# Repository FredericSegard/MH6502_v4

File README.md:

# MH6502-4
 This is my masterpiece MH6502-4.

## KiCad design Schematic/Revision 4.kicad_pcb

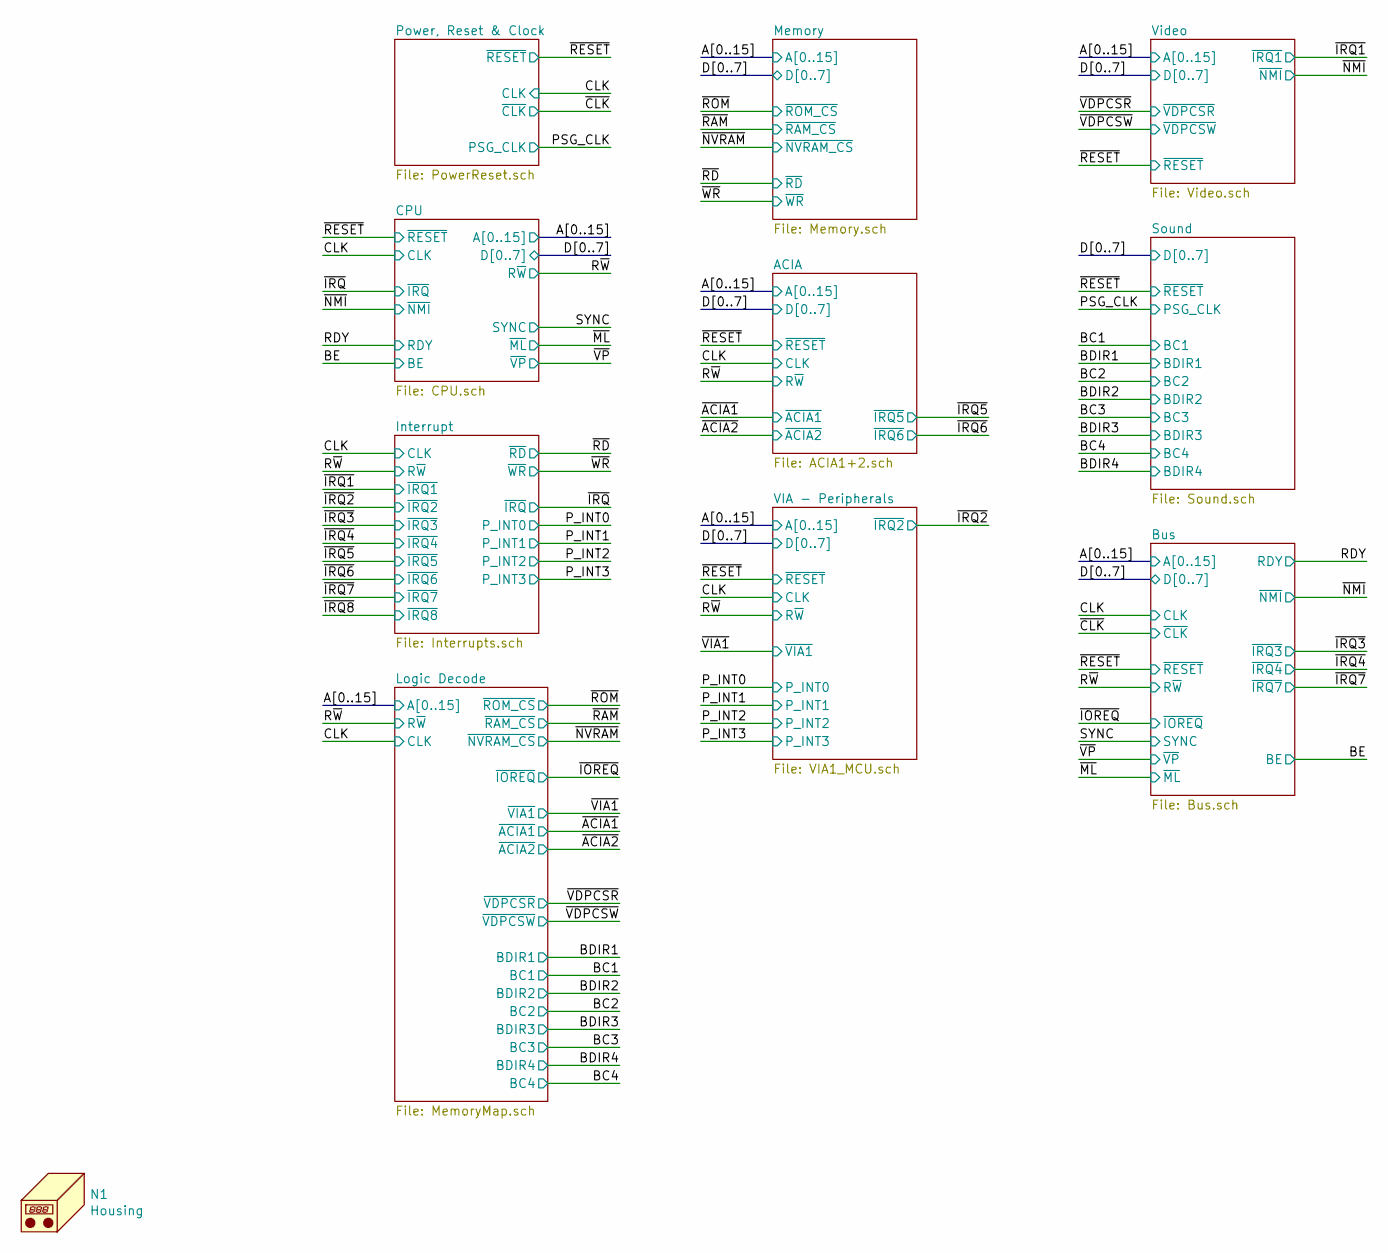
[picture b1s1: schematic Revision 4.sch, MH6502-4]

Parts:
N1: Housing; 18877_Housing

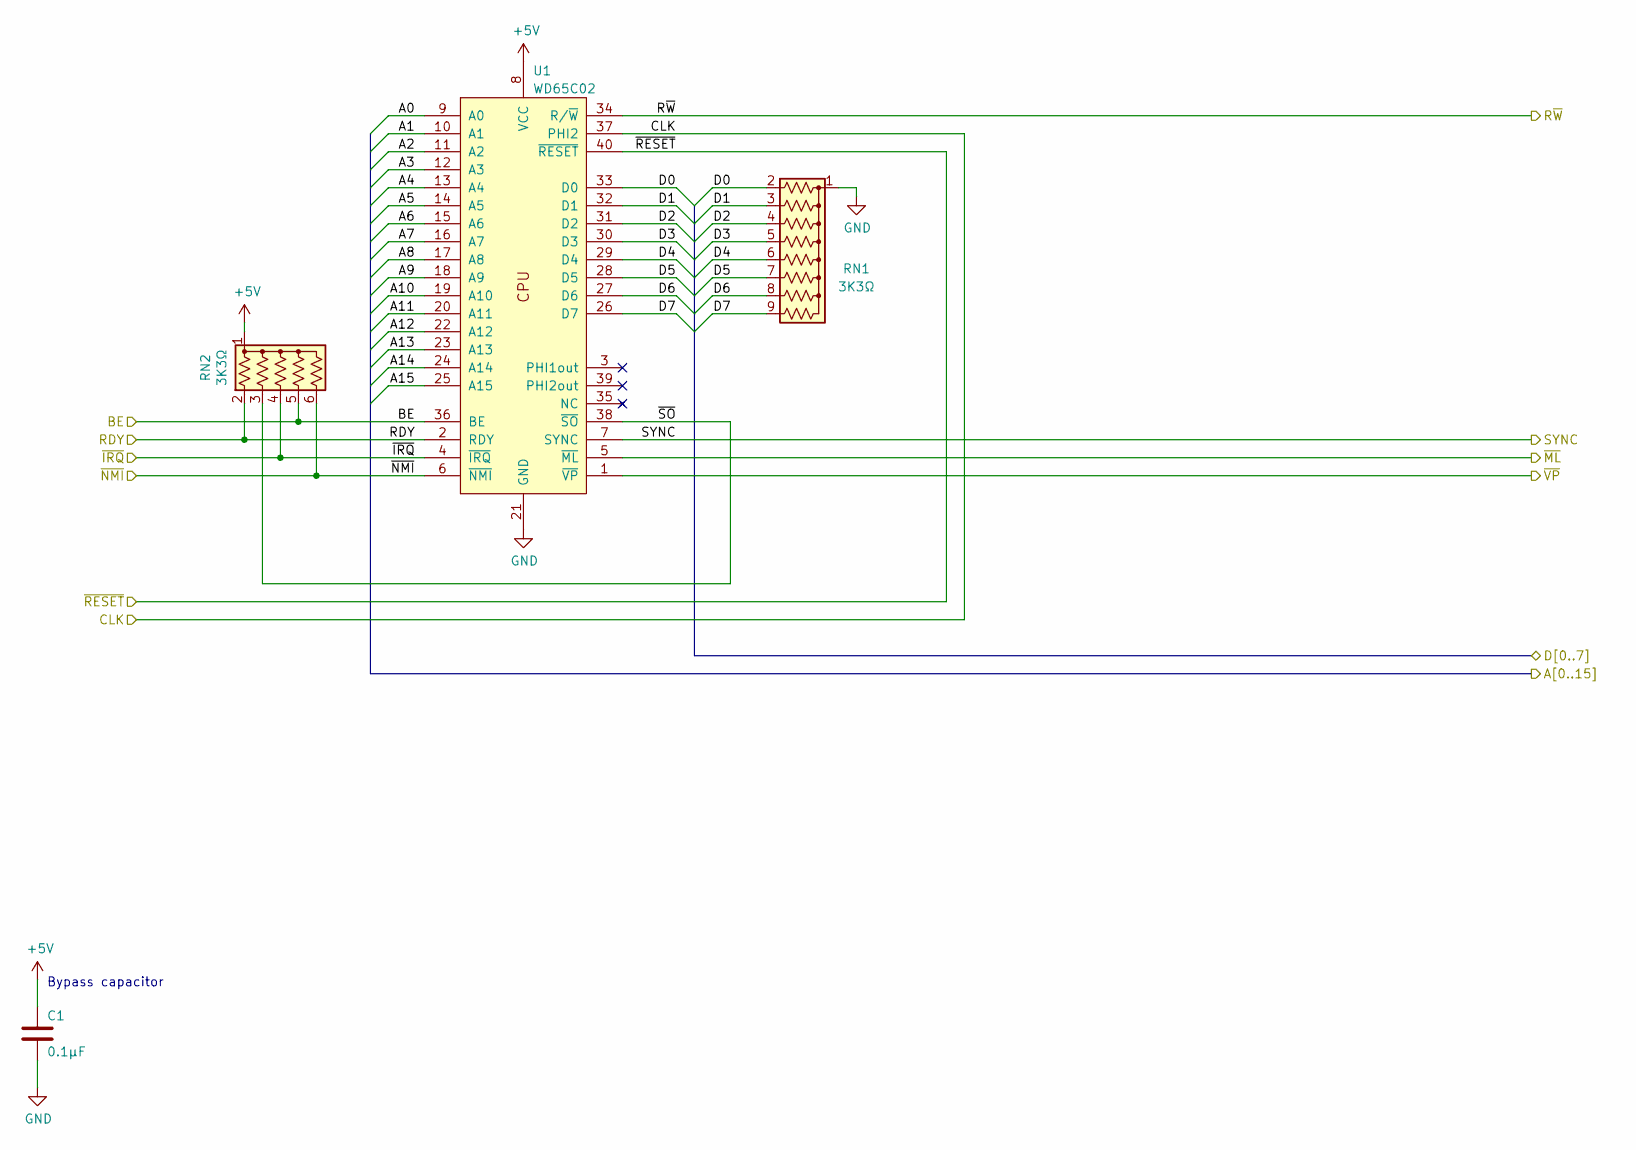
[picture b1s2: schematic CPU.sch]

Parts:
C1: 0.1µF; C_Disc_D3.0mm_W1.6mm_P2.50mm
RN1: 3K3Ω; R_Array_SIP9
RN2: 3K3Ω; R_Array_SIP6
U1: WD65C02; DIP-40_W15.24mm_Socket

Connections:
+5V: C1.1, RN2.1 (common), U1.8 (VCC); also elsewhere on the board
/ACIA/A0: U1.9 (A0); also elsewhere on the board
/ACIA/A1: U1.10 (A1); also elsewhere on the board
/ACIA/D0: RN1.2 (R1), U1.33 (D0); also elsewhere on the board
/ACIA/D1: RN1.3 (R2), U1.32 (D1); also elsewhere on the board
/ACIA/D2: RN1.4 (R3), U1.31 (D2); also elsewhere on the board
/ACIA/D3: RN1.5 (R4), U1.30 (D3); also elsewhere on the board
/ACIA/D4: RN1.6 (R5), U1.29 (D4); also elsewhere on the board
/ACIA/D5: RN1.7 (R6), U1.28 (D5); also elsewhere on the board
/ACIA/D6: RN1.8 (R7), U1.27 (D6); also elsewhere on the board
/ACIA/D7: RN1.9 (R8), U1.26 (D7); also elsewhere on the board
/BE: RN2.5 (R4), U1.36 (BE); also elsewhere on the board
/Bus/A2: U1.11 (A2); also elsewhere on the board
/Bus/A3: U1.12 (A3); also elsewhere on the board
/Bus/A4: U1.13 (A4); also elsewhere on the board
/Bus/A5: U1.14 (A5); also elsewhere on the board
/Bus/A6: U1.15 (A6); also elsewhere on the board
/Bus/A7: U1.16 (A7); also elsewhere on the board
/CLK: U1.37 (PHI2); also elsewhere on the board
/CPU/A8: U1.17 (A8); also elsewhere on the board
/CPU/A9: U1.18 (A9); also elsewhere on the board
/CPU/A10: U1.19 (A10); also elsewhere on the board
/CPU/A11: U1.20 (A11); also elsewhere on the board
/CPU/A12: U1.22 (A12); also elsewhere on the board
/CPU/A13: U1.23 (A13); also elsewhere on the board
/CPU/A14: U1.24 (A14); also elsewhere on the board
/CPU/A15: U1.25 (A15); also elsewhere on the board
/CPU/~SO: RN2.3 (R2), U1.38 (~SO)
/RDY: RN2.2 (R1), U1.2 (RDY); also elsewhere on the board
/R~W: U1.34 (R/~W); also elsewhere on the board
/SYNC: U1.7 (SYNC); also elsewhere on the board
/~IRQ: RN2.4 (R3), U1.4 (~IRQ); also elsewhere on the board
/~ML: U1.5 (~ML); also elsewhere on the board
/~NMI: RN2.6 (R5), U1.6 (~NMI); also elsewhere on the board
/~RESET: U1.40 (~RESET); also elsewhere on the board
/~VP: U1.1 (~VP); also elsewhere on the board
GND: C1.2, RN1.1 (common), U1.21 (GND); also elsewhere on the board

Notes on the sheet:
Bypass capacitor

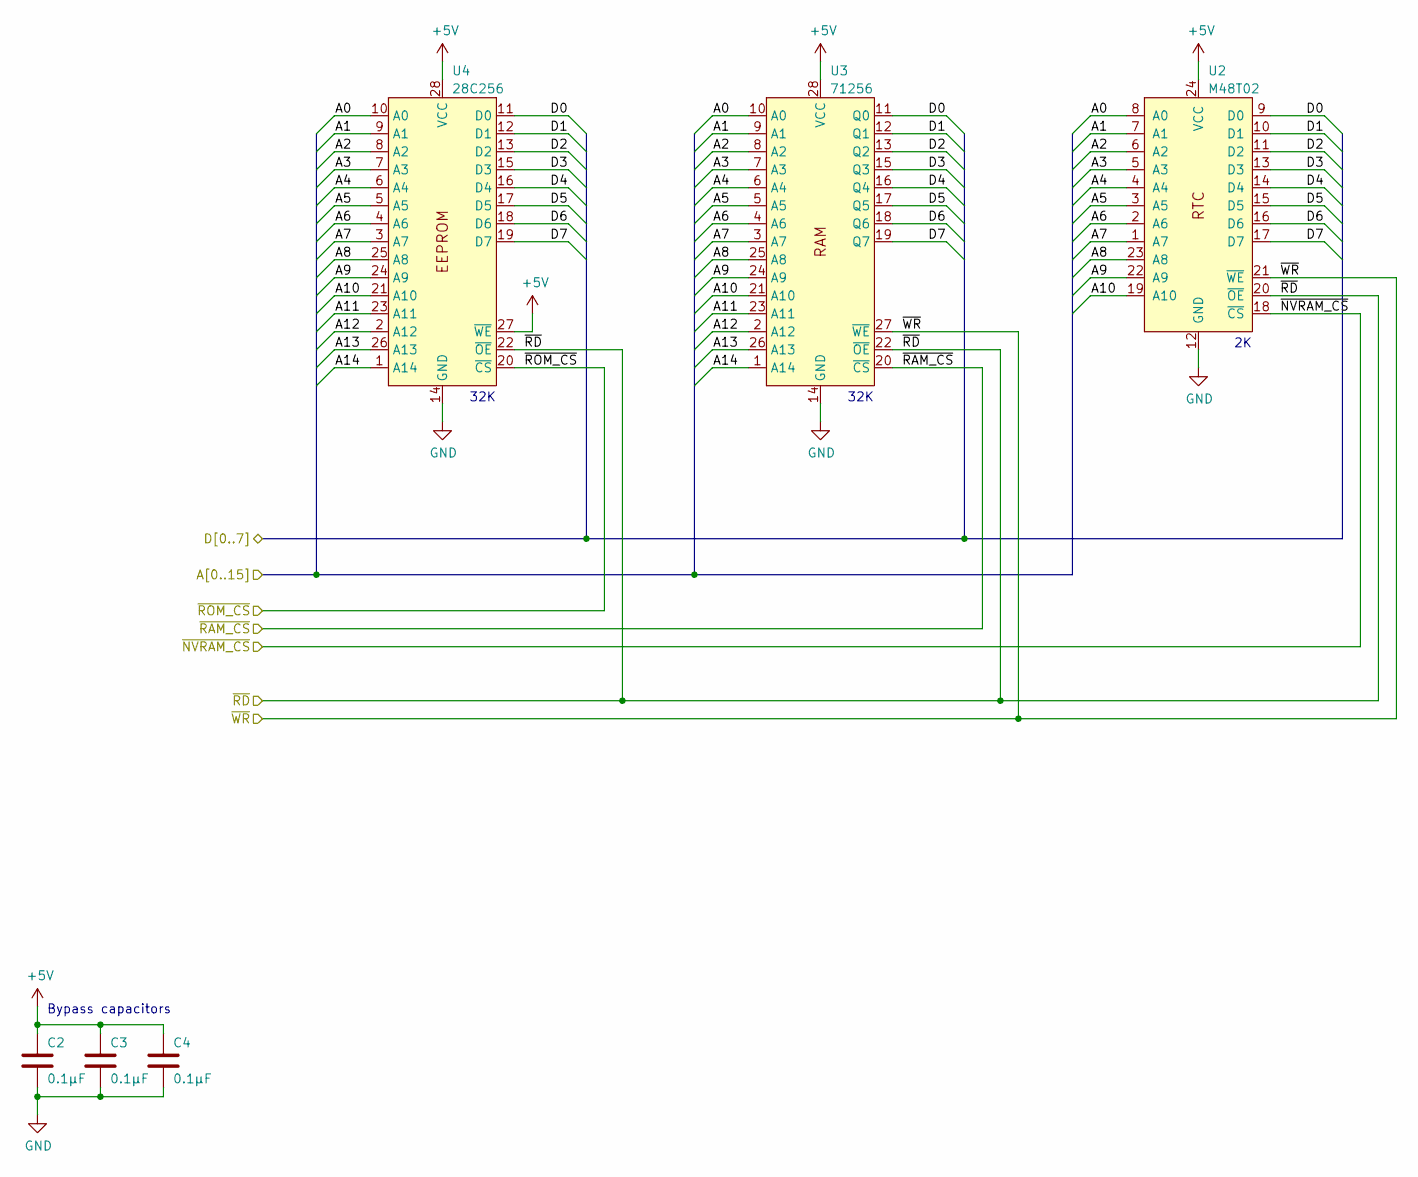
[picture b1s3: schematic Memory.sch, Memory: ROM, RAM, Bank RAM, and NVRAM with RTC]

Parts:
C2, C3, C4: 0.1µF; C_Disc_D3.0mm_W1.6mm_P2.50mm
U2: M48T02; DIP-24_W15.24mm_Socket
U3: 71256; DIP-28_W7.62mm_Socket
U4: 28C256; ZIF-28

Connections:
+5V: C2.1, C3.1, C4.1, U2.24 (VCC), U3.28 (VCC), U4.27 (~WE), U4.28 (VCC); also elsewhere on the board
/ACIA/A0: U2.8 (A0), U3.10 (A0), U4.10 (A0); also elsewhere on the board
/ACIA/A1: U2.7 (A1), U3.9 (A1), U4.9 (A1); also elsewhere on the board
/ACIA/D0: U2.9 (D0), U3.11 (Q0), U4.11 (D0); also elsewhere on the board
/ACIA/D1: U2.10 (D1), U3.12 (Q1), U4.12 (D1); also elsewhere on the board
/ACIA/D2: U2.11 (D2), U3.13 (Q2), U4.13 (D2); also elsewhere on the board
/ACIA/D3: U2.13 (D3), U3.15 (Q3), U4.15 (D3); also elsewhere on the board
/ACIA/D4: U2.14 (D4), U3.16 (Q4), U4.16 (D4); also elsewhere on the board
/ACIA/D5: U2.15 (D5), U3.17 (Q5), U4.17 (D5); also elsewhere on the board
/ACIA/D6: U2.16 (D6), U3.18 (Q6), U4.18 (D6); also elsewhere on the board
/ACIA/D7: U2.17 (D7), U3.19 (Q7), U4.19 (D7); also elsewhere on the board
/Bus/A2: U2.6 (A2), U3.8 (A2), U4.8 (A2); also elsewhere on the board
/Bus/A3: U2.5 (A3), U3.7 (A3), U4.7 (A3); also elsewhere on the board
/Bus/A4: U2.4 (A4), U3.6 (A4), U4.6 (A4); also elsewhere on the board
/Bus/A5: U2.3 (A5), U3.5 (A5), U4.5 (A5); also elsewhere on the board
/Bus/A6: U2.2 (A6), U3.4 (A6), U4.4 (A6); also elsewhere on the board
/Bus/A7: U2.1 (A7), U3.3 (A7), U4.3 (A7); also elsewhere on the board
/CPU/A8: U2.23 (A8), U3.25 (A8), U4.25 (A8); also elsewhere on the board
/CPU/A9: U2.22 (A9), U3.24 (A9), U4.24 (A9); also elsewhere on the board
/CPU/A10: U2.19 (A10), U3.21 (A10), U4.21 (A10); also elsewhere on the board
/CPU/A11: U3.23 (A11), U4.23 (A11); also elsewhere on the board
/CPU/A12: U3.2 (A12), U4.2 (A12); also elsewhere on the board
/CPU/A13: U3.26 (A13), U4.26 (A13); also elsewhere on the board
/CPU/A14: U3.1 (A14), U4.1 (A14); also elsewhere on the board
/~NVRAM: U2.18 (~CS); also elsewhere on the board
/~RAM: U3.20 (~CS); also elsewhere on the board
/~RD: U2.20 (~OE), U3.22 (~OE), U4.22 (~OE); also elsewhere on the board
/~ROM: U4.20 (~CS); also elsewhere on the board
/~WR: U2.21 (~WE), U3.27 (~WE); also elsewhere on the board
GND: C2.2, C3.2, C4.2, U2.12 (GND), U3.14 (GND), U4.14 (GND); also elsewhere on the board

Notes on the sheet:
32K
Bypass capacitors

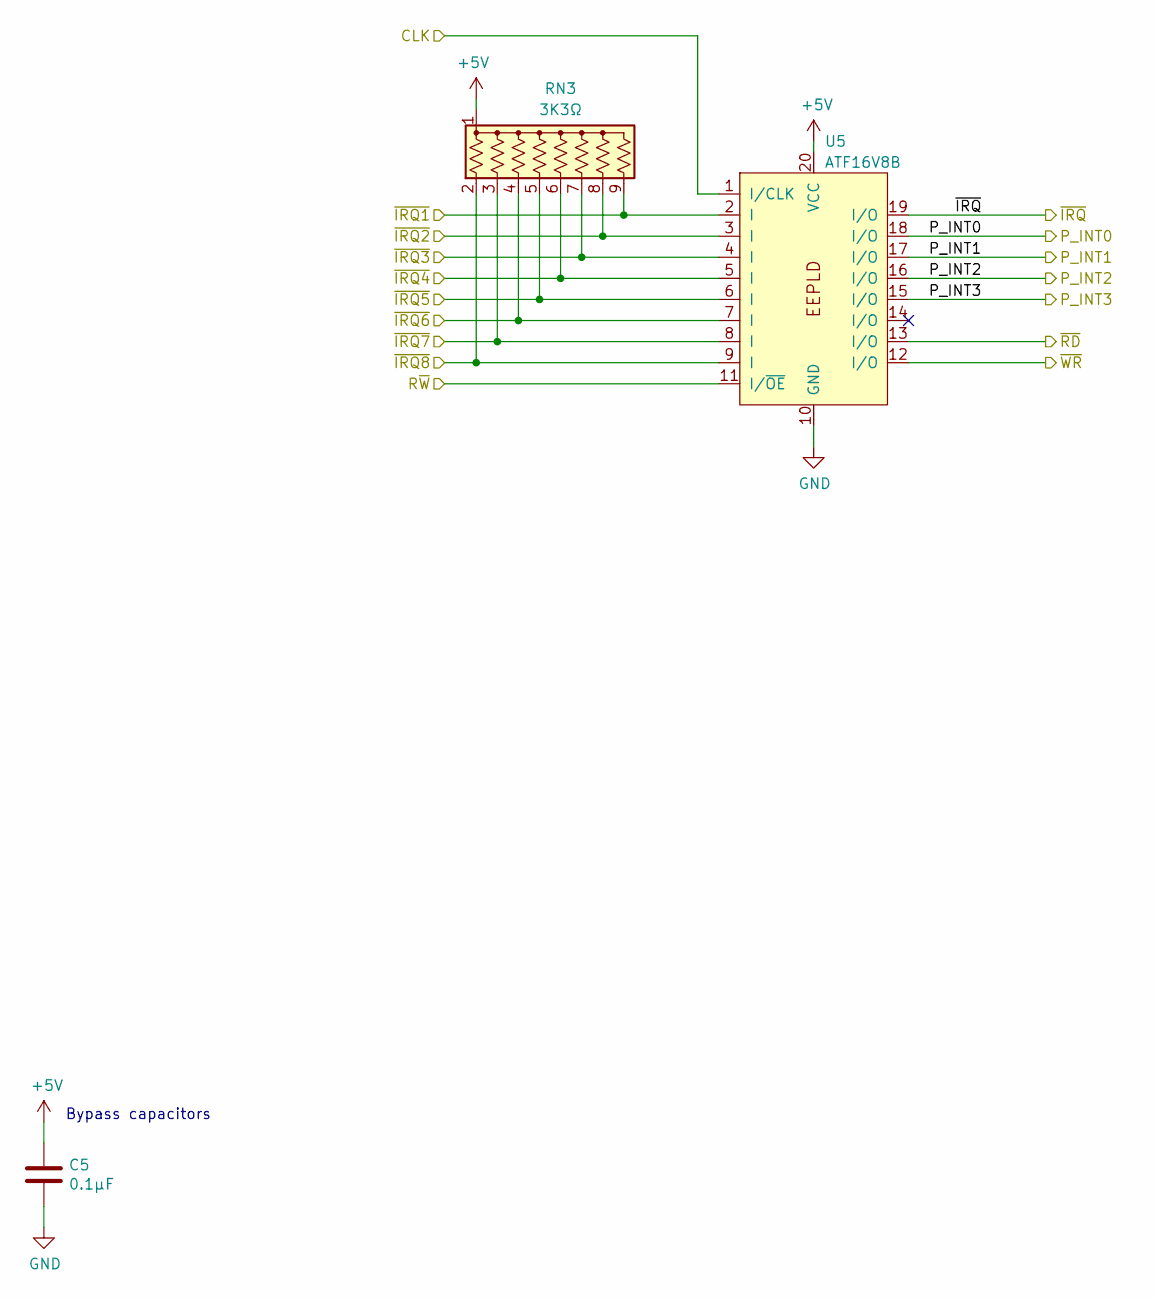
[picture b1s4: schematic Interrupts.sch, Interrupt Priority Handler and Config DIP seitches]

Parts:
C5: 0.1µF; C_Disc_D3.0mm_W1.6mm_P2.50mm
RN3: 3K3Ω; R_Array_SIP9
U5: ATF16V8B; DIP-20_W7.62mm_Socket

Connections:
+5V: C5.1, RN3.1 (common), U5.20 (VCC); also elsewhere on the board
/CLK: U5.1 (I/CLK); also elsewhere on the board
/P_INT0: U5.18 (I/O); also elsewhere on the board
/P_INT1: U5.17 (I/O); also elsewhere on the board
/P_INT2: U5.16 (I/O); also elsewhere on the board
/P_INT3: U5.15 (I/O); also elsewhere on the board
/R~W: U5.11 (I/~OE); also elsewhere on the board
/~IRQ: U5.19 (I/O); also elsewhere on the board
/~IRQ1: RN3.9 (R8), U5.2 (I); also elsewhere on the board
/~IRQ2: RN3.8 (R7), U5.3 (I); also elsewhere on the board
/~IRQ3: RN3.7 (R6), U5.4 (I); also elsewhere on the board
/~IRQ4: RN3.6 (R5), U5.5 (I); also elsewhere on the board
/~IRQ5: RN3.5 (R4), U5.6 (I); also elsewhere on the board
/~IRQ6: RN3.4 (R3), U5.7 (I); also elsewhere on the board
/~IRQ7: RN3.3 (R2), U5.8 (I); also elsewhere on the board
/~IRQ8: RN3.2 (R1), U5.9 (I)
/~RD: U5.13 (I/O); also elsewhere on the board
/~WR: U5.12 (I/O); also elsewhere on the board
GND: C5.2, U5.10 (GND); also elsewhere on the board

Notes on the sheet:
Bypass capacitors

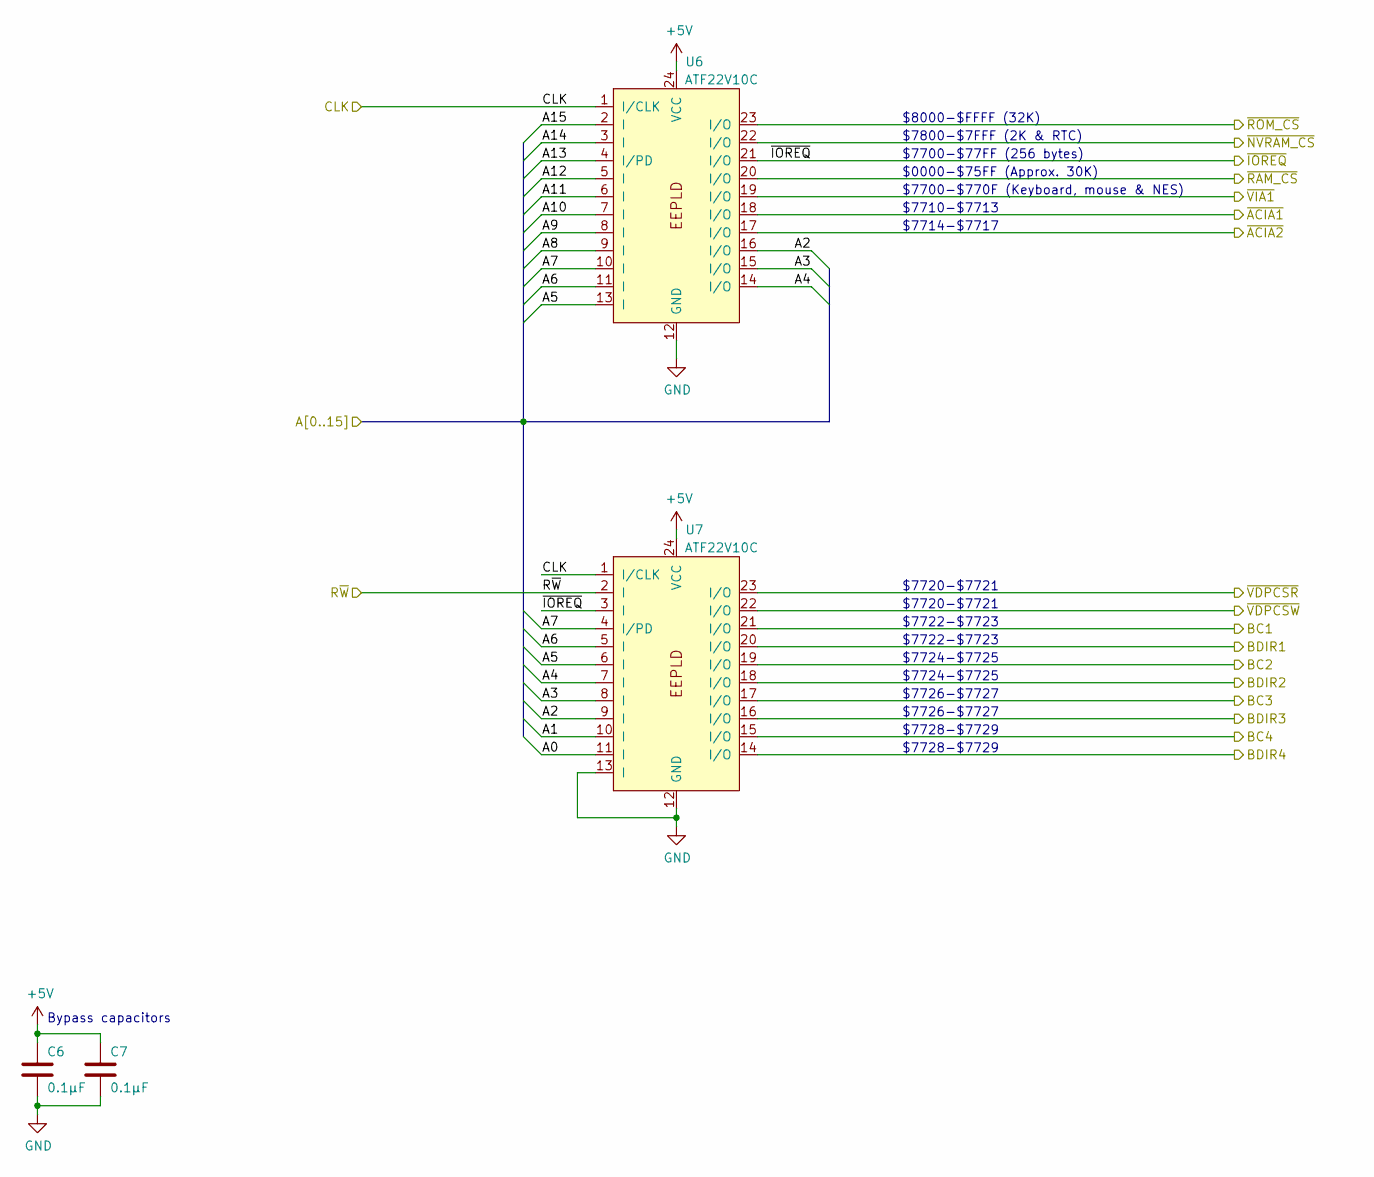
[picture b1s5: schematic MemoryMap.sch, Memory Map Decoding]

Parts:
C6, C7: 0.1µF; C_Disc_D3.0mm_W1.6mm_P2.50mm
U6, U7: ATF22V10C; DIP-24_W7.62mm_Socket

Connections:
+5V: C6.1, C7.1, U6.24 (VCC), U7.24 (VCC); also elsewhere on the board
/ACIA/A0: U7.11 (I); also elsewhere on the board
/ACIA/A1: U7.10 (I); also elsewhere on the board
/BC1: U7.21 (I/O); also elsewhere on the board
/BC2: U7.19 (I/O); also elsewhere on the board
/BC3: U7.17 (I/O); also elsewhere on the board
/BC4: U7.15 (I/O); also elsewhere on the board
/BDIR1: U7.20 (I/O); also elsewhere on the board
/BDIR2: U7.18 (I/O); also elsewhere on the board
/BDIR3: U7.16 (I/O); also elsewhere on the board
/BDIR4: U7.14 (I/O); also elsewhere on the board
/Bus/A2: U6.16 (I/O), U7.9 (I); also elsewhere on the board
/Bus/A3: U6.15 (I/O), U7.8 (I); also elsewhere on the board
/Bus/A4: U6.14 (I/O), U7.7 (I); also elsewhere on the board
/Bus/A5: U6.13 (I), U7.6 (I); also elsewhere on the board
/Bus/A6: U6.11 (I), U7.5 (I); also elsewhere on the board
/Bus/A7: U6.10 (I), U7.4 (I/PD); also elsewhere on the board
/CLK: U6.1 (I/CLK), U7.1 (I/CLK); also elsewhere on the board
/CPU/A8: U6.9 (I); also elsewhere on the board
/CPU/A9: U6.8 (I); also elsewhere on the board
/CPU/A10: U6.7 (I); also elsewhere on the board
/CPU/A11: U6.6 (I); also elsewhere on the board
/CPU/A12: U6.5 (I); also elsewhere on the board
/CPU/A13: U6.4 (I/PD); also elsewhere on the board
/CPU/A14: U6.3 (I); also elsewhere on the board
/CPU/A15: U6.2 (I); also elsewhere on the board
/R~W: U7.2 (I); also elsewhere on the board
/~ACIA1: U6.18 (I/O); also elsewhere on the board
/~ACIA2: U6.17 (I/O); also elsewhere on the board
/~IOREQ: U6.21 (I/O), U7.3 (I); also elsewhere on the board
/~NVRAM: U6.22 (I/O); also elsewhere on the board
/~RAM: U6.20 (I/O); also elsewhere on the board
/~ROM: U6.23 (I/O); also elsewhere on the board
/~VDPCSR: U7.23 (I/O); also elsewhere on the board
/~VDPCSW: U7.22 (I/O); also elsewhere on the board
/~VIA1: U6.19 (I/O); also elsewhere on the board
GND: C6.2, C7.2, U6.12 (GND), U7.12 (GND), U7.13 (I); also elsewhere on the board

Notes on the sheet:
Bypass capacitors
$8000-$FFFF (32K)
$7800-$7FFF (2K & RTC)
$7700-$77FF (256 bytes)
$0000-$75FF (Approx. 30K)
$7714-$7717
$7700-$770F (Keyboard, mouse & NES)
$7720-$7721
$7722-$7723
$7724-$7725
$7726-$7727
$7710-$7713
$7728-$7729

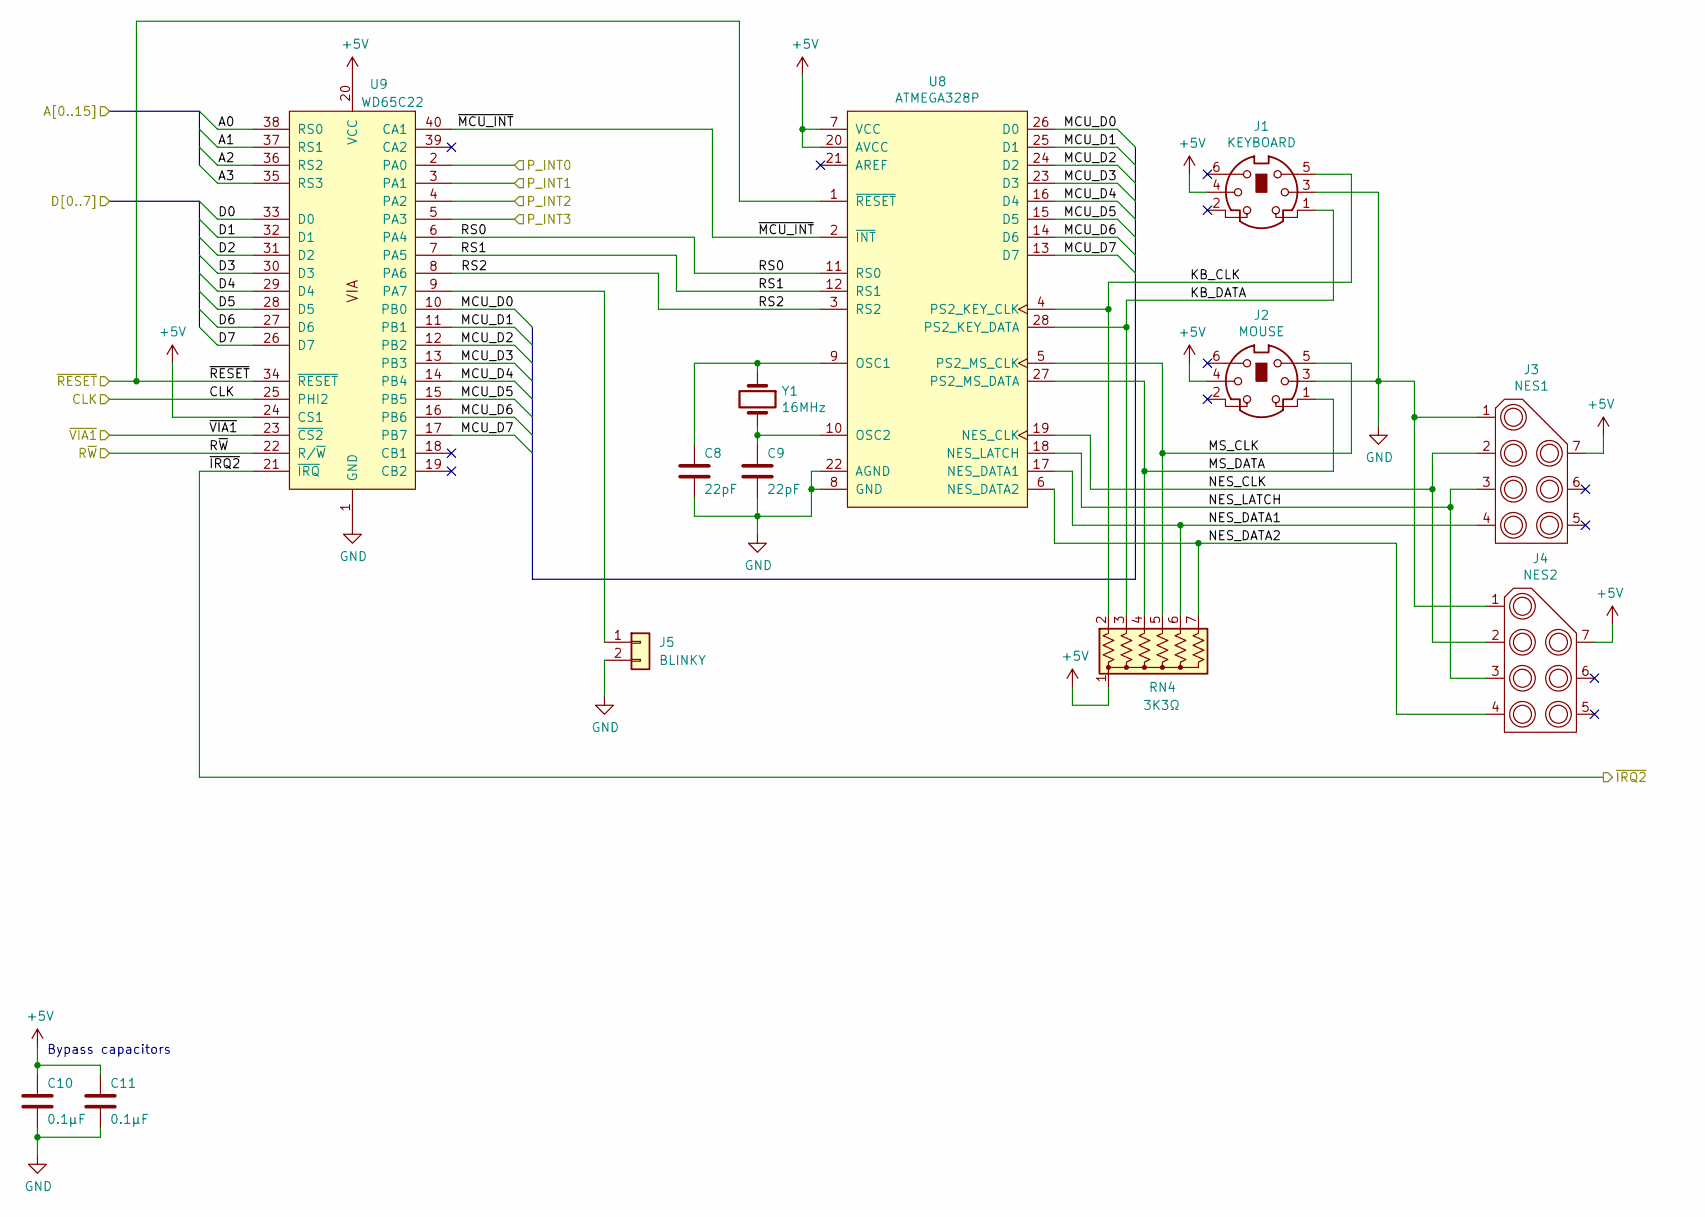
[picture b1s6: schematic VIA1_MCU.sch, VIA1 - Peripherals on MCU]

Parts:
C8, C9: 22pF; C_Disc_D3.0mm_W1.6mm_P2.50mm
C10, C11: 0.1µF; C_Disc_D3.0mm_W1.6mm_P2.50mm
J1: KEYBOARD; Mini-DIN_6p
J2: MOUSE; Mini-DIN_6p
J3: NES1; NES_Connector
J4: NES2; NES_Connector
J5: BLINKY; PinHeader_1x02_P2.54mm_Vertical
RN4: 3K3Ω; R_Array_SIP7
U8: ATMEGA328P; DIP-28_W7.62mm_Socket
U9: WD65C22; DIP-40_W15.24mm_Socket
Y1: 16MHz; Crystal_HC18-U_Vertical

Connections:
+5V: C10.1, C11.1, J1.4, J2.4, J3.7, J4.7, RN4.1 (common), U8.7 (VCC), U8.20 (AVCC), U9.20 (VCC), U9.24 (CS1); also elsewhere on the board
/ACIA/A0: U9.38 (RS0); also elsewhere on the board
/ACIA/A1: U9.37 (RS1); also elsewhere on the board
/ACIA/D0: U9.33 (D0); also elsewhere on the board
/ACIA/D1: U9.32 (D1); also elsewhere on the board
/ACIA/D2: U9.31 (D2); also elsewhere on the board
/ACIA/D3: U9.30 (D3); also elsewhere on the board
/ACIA/D4: U9.29 (D4); also elsewhere on the board
/ACIA/D5: U9.28 (D5); also elsewhere on the board
/ACIA/D6: U9.27 (D6); also elsewhere on the board
/ACIA/D7: U9.26 (D7); also elsewhere on the board
/Bus/A2: U9.36 (RS2); also elsewhere on the board
/Bus/A3: U9.35 (RS3); also elsewhere on the board
/CLK: U9.25 (PHI2); also elsewhere on the board
/P_INT0: U9.2 (PA0); also elsewhere on the board
/P_INT1: U9.3 (PA1); also elsewhere on the board
/P_INT2: U9.4 (PA2); also elsewhere on the board
/P_INT3: U9.5 (PA3); also elsewhere on the board
/R~W: U9.22 (R/~W); also elsewhere on the board
/VIA - Peripherals/KB_CLK: J1.5, RN4.2 (R1), U8.4 (PS2_KEY_CLK)
/VIA - Peripherals/KB_DATA: J1.1, RN4.3 (R2), U8.28 (PS2_KEY_DATA)
/VIA - Peripherals/MCU_D0: U8.26 (D0), U9.10 (PB0)
/VIA - Peripherals/MCU_D1: U8.25 (D1), U9.11 (PB1)
/VIA - Peripherals/MCU_D2: U8.24 (D2), U9.12 (PB2)
/VIA - Peripherals/MCU_D3: U8.23 (D3), U9.13 (PB3)
/VIA - Peripherals/MCU_D4: U8.16 (D4), U9.14 (PB4)
/VIA - Peripherals/MCU_D5: U8.15 (D5), U9.15 (PB5)
/VIA - Peripherals/MCU_D6: U8.14 (D6), U9.16 (PB6)
/VIA - Peripherals/MCU_D7: U8.13 (D7), U9.17 (PB7)
/VIA - Peripherals/MS_CLK: J2.5, RN4.5 (R4), U8.5 (PS2_MS_CLK)
/VIA - Peripherals/MS_DATA: J2.1, RN4.4 (R3), U8.27 (PS2_MS_DATA)
/VIA - Peripherals/NES_CLK: J3.2, J4.2, U8.19 (NES_CLK)
/VIA - Peripherals/NES_DATA1: J3.4, RN4.6 (R5), U8.17 (NES_DATA1)
/VIA - Peripherals/NES_DATA2: J4.4, RN4.7 (R6), U8.6 (NES_DATA2)
/VIA - Peripherals/NES_LATCH: J3.3, J4.3, U8.18 (NES_LATCH)
/VIA - Peripherals/RS0: U8.11 (RS0), U9.6 (PA4)
/VIA - Peripherals/RS1: U8.12 (RS1), U9.7 (PA5)
/VIA - Peripherals/RS2: U8.3 (RS2), U9.8 (PA6)
/VIA - Peripherals/~MCU_INT: U8.2 (~INT), U9.40 (CA1)
/~IRQ2: U9.21 (~IRQ); also elsewhere on the board
/~RESET: U8.1 (~RESET), U9.34 (~RESET); also elsewhere on the board
/~VIA1: U9.23 (~CS2); also elsewhere on the board
GND: C8.2, C9.2, C10.2, C11.2, J1.3, J2.3, J3.1, J4.1, J5.2, U8.8 (GND), U8.22 (AGND), U9.1 (GND); also elsewhere on the board
unnamed: C8.1, U8.9 (OSC1), Y1.1
unnamed: C9.1, U8.10 (OSC2), Y1.2
unnamed: J5.1, U9.9 (PA7)

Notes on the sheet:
Bypass capacitors

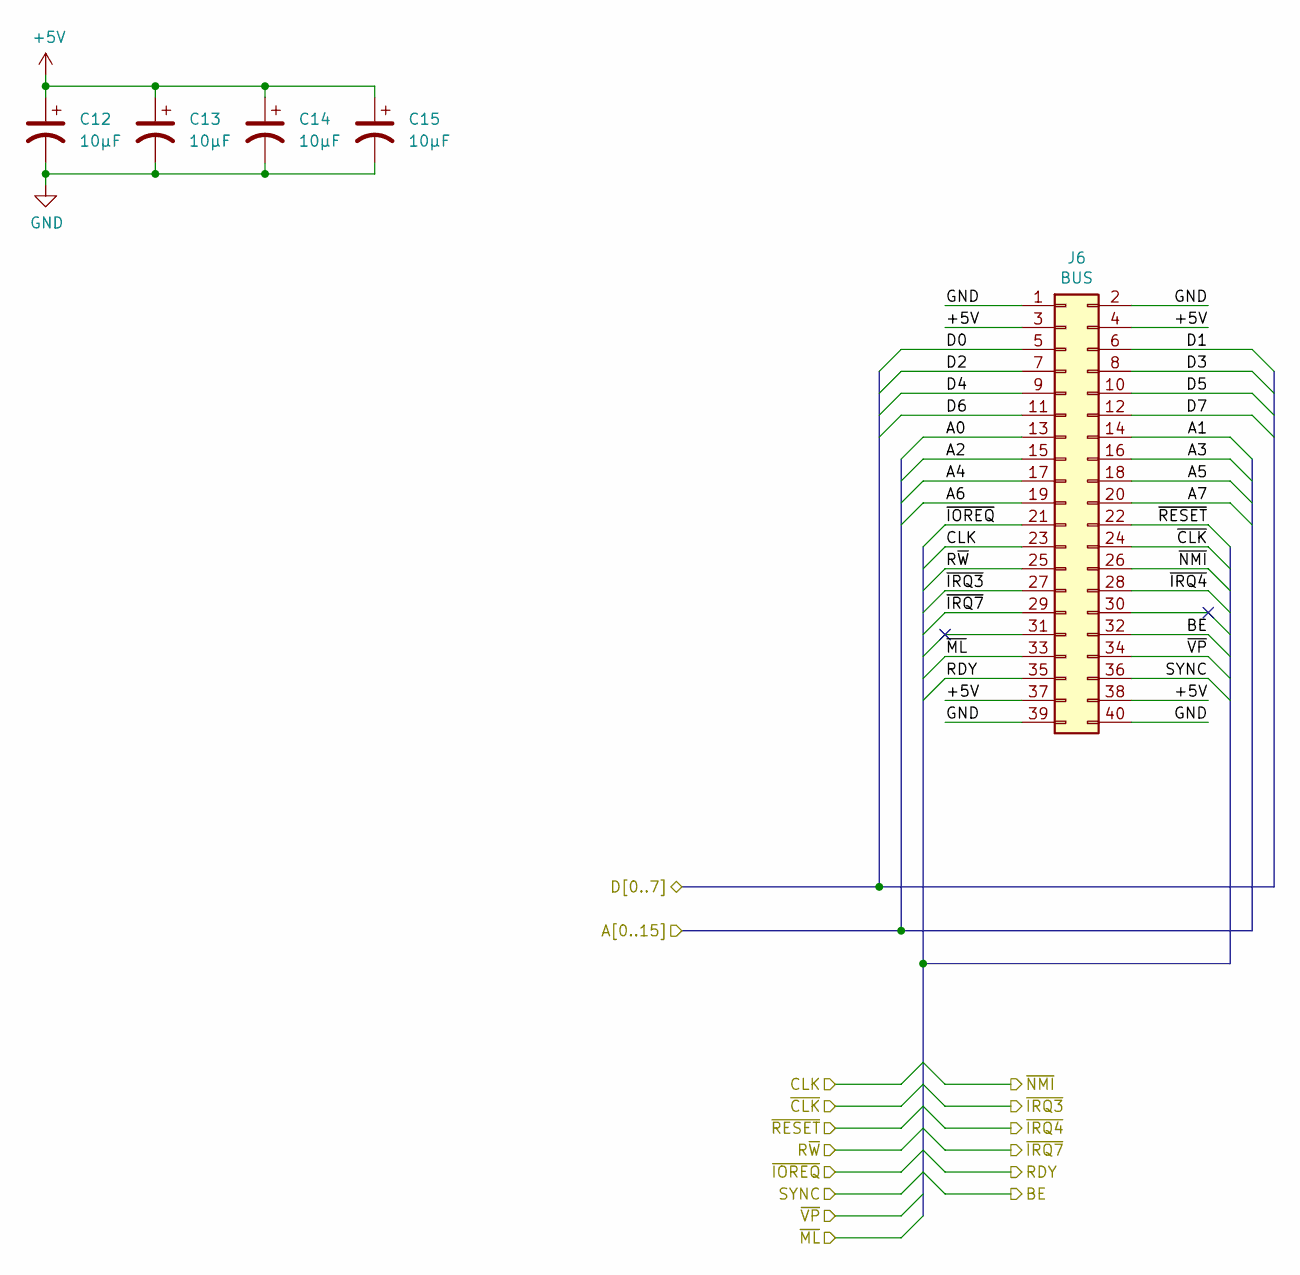
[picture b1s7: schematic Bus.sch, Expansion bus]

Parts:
C12, C13, C14, C15: 10µF; CP_Radial_D6.3mm_P2.50mm
J6: BUS; PinHeader_2x20_P2.54mm_Vertical

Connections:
+5V: C12.1, C13.1, C14.1, C15.1, J6.3, J6.4, J6.37, J6.38; also elsewhere on the board
/ACIA/A0: J6.13; also elsewhere on the board
/ACIA/A1: J6.14; also elsewhere on the board
/ACIA/D0: J6.5; also elsewhere on the board
/ACIA/D1: J6.6; also elsewhere on the board
/ACIA/D2: J6.7; also elsewhere on the board
/ACIA/D3: J6.8; also elsewhere on the board
/ACIA/D4: J6.9; also elsewhere on the board
/ACIA/D5: J6.10; also elsewhere on the board
/ACIA/D6: J6.11; also elsewhere on the board
/ACIA/D7: J6.12; also elsewhere on the board
/BE: J6.32; also elsewhere on the board
/Bus/A2: J6.15; also elsewhere on the board
/Bus/A3: J6.16; also elsewhere on the board
/Bus/A4: J6.17; also elsewhere on the board
/Bus/A5: J6.18; also elsewhere on the board
/Bus/A6: J6.19; also elsewhere on the board
/Bus/A7: J6.20; also elsewhere on the board
/CLK: J6.23; also elsewhere on the board
/RDY: J6.35; also elsewhere on the board
/R~W: J6.25; also elsewhere on the board
/SYNC: J6.36; also elsewhere on the board
/~CLK: J6.24; also elsewhere on the board
/~IOREQ: J6.21; also elsewhere on the board
/~IRQ3: J6.27; also elsewhere on the board
/~IRQ4: J6.28; also elsewhere on the board
/~IRQ7: J6.29; also elsewhere on the board
/~ML: J6.33; also elsewhere on the board
/~NMI: J6.26; also elsewhere on the board
/~RESET: J6.22; also elsewhere on the board
/~VP: J6.34; also elsewhere on the board
GND: C12.2, C13.2, C14.2, C15.2, J6.1, J6.2, J6.39, J6.40; also elsewhere on the board

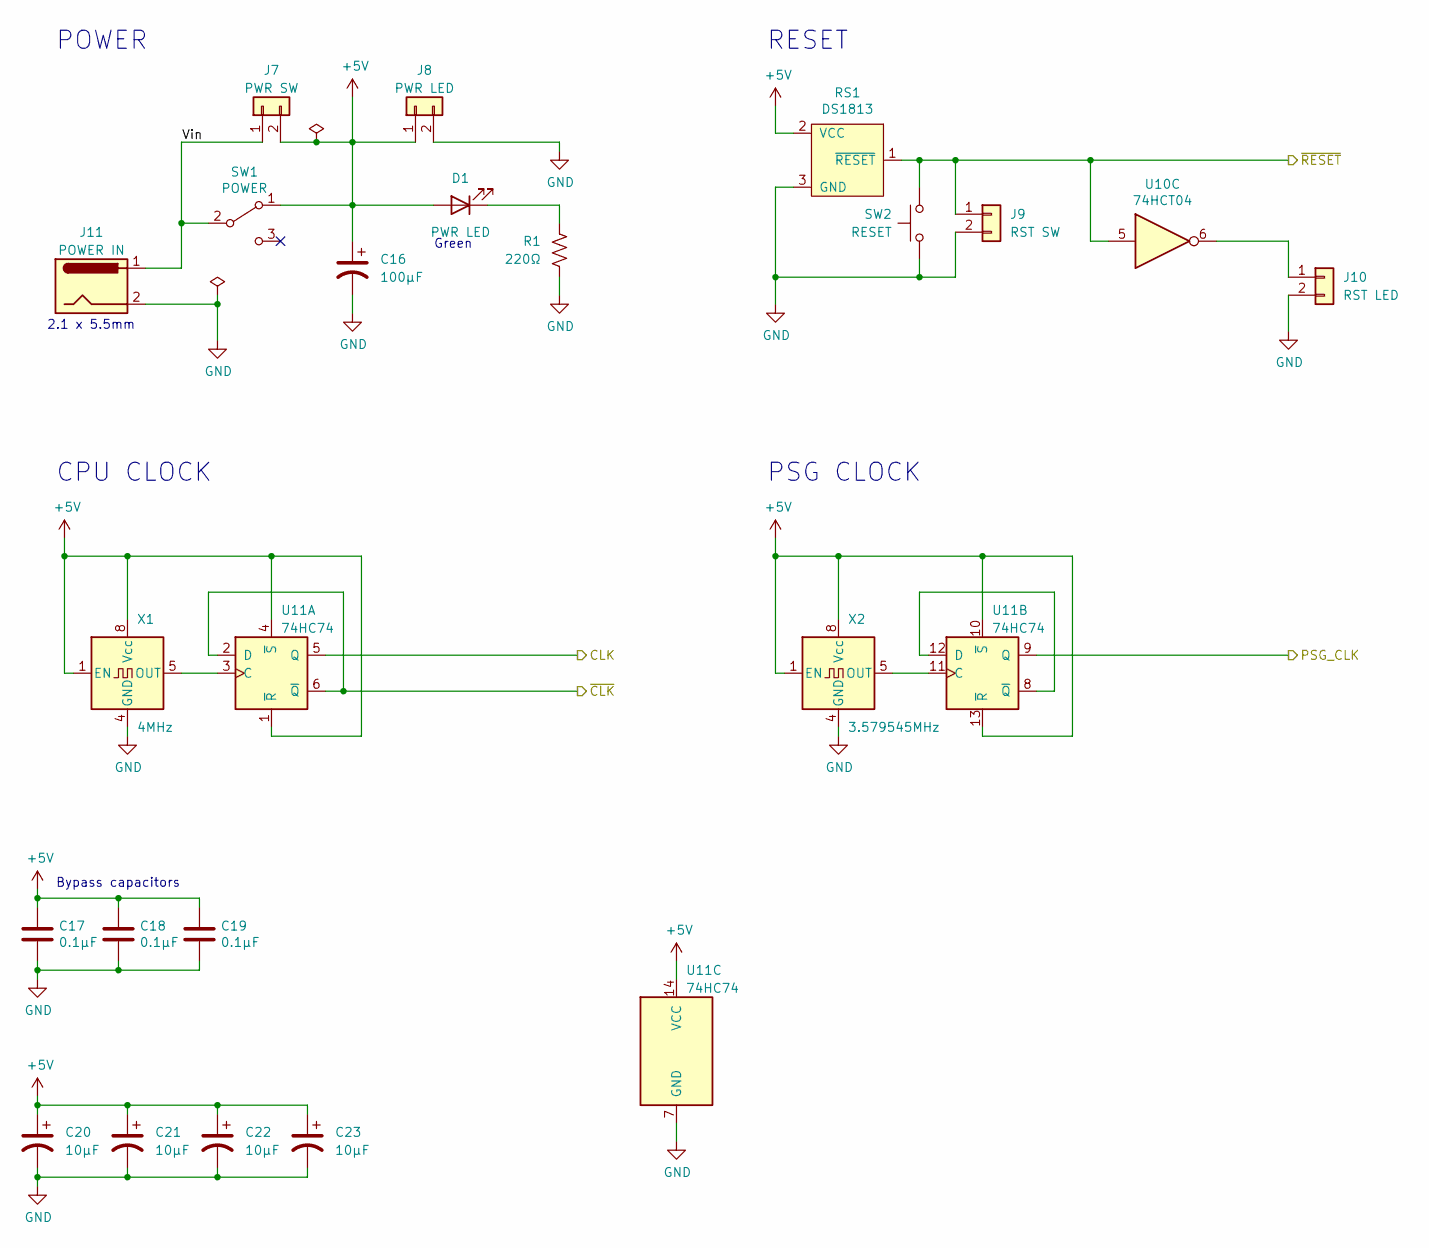
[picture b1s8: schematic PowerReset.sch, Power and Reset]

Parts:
C16: 100µF; CP_Radial_D8.0mm_P3.80mm
C17, C18, C19: 0.1µF; C_Disc_D3.0mm_W1.6mm_P2.50mm
C20, C21, C22, C23: 10µF; CP_Radial_D6.3mm_P2.50mm
D1: PWR LED; LED_D3.0mm
J7: PWR SW; PinHeader_1x02_P2.54mm_Vertical
J8: PWR LED; PinHeader_1x02_P2.54mm_Vertical
J9: RST SW; PinHeader_1x02_P2.54mm_Vertical
J10: RST LED; PinHeader_1x02_P2.54mm_Vertical
J11: POWER IN; BarrelJack_Horizontal
R1: 220Ω; R_Axial_DIN0207_L6.3mm_D2.5mm_P10.16mm_Horizontal
RS1: DS1813; TO-92L_Inline_Wide
SW1: POWER; Microswitch_3mm_spacing_2
SW2: RESET; SW_PUSH_6mm
U10: 74HCT04; DIP-14_W7.62mm_Socket
U11: 74HC74; DIP-14_W7.62mm_Socket
X1: 4MHz; Oscillator_DIP-8
X2: 3.579545MHz; Oscillator_DIP-8

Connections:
+5V: C16.1, C17.1, C18.1, C19.1, C20.1, C21.1, C22.1, C23.1, D1.2 (A), J7.2, J8.1, RS1.2 (VCC), SW1.1 (A), U11.1 (~R), U11.4 (~S), U11.10 (~S), U11.13 (~R), U11.14 (VCC), X1.1 (EN), X1.8 (Vcc), X2.1 (EN), X2.8 (Vcc); also elsewhere on the board
/CLK: U11.5 (Q); also elsewhere on the board
/PSG_CLK: U11.9 (Q); also elsewhere on the board
/Power, Reset & Clock/Vin: J7.1, J11.1, SW1.2 (B)
/~CLK: U11.2 (D), U11.6 (~Q); also elsewhere on the board
/~RESET: J9.1, RS1.1 (~RESET), SW2.1, U10.5; also elsewhere on the board
GND: C16.2, C17.2, C18.2, C19.2, C20.2, C21.2, C22.2, C23.2, J8.2, J9.2, J10.2, J11.2, R1.1, RS1.3 (GND), SW2.2, U11.7 (GND), X1.4 (GND), X2.4 (GND); also elsewhere on the board
unnamed: D1.1 (K), R1.2
unnamed: J10.1, U10.6
unnamed: U11.3 (C), X1.5 (OUT)
unnamed: U11.11 (C), X2.5 (OUT)
unnamed: U11.8 (~Q), U11.12 (D)

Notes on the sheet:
Bypass capacitors
RESET
CPU CLOCK
PSG CLOCK
POWER
Green
2.1 x 5.5mm
